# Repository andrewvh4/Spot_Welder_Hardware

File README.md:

# Spot_Welder_Hardware
A Design for a low-cost spot welder used in electronics assembly

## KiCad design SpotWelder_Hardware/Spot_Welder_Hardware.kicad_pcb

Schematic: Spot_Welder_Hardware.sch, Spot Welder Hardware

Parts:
BZ1: Buzzer; BUZZER_SMI_1324_TW_5V_2_R; Part Number 668-1336-1-ND
C1, C2, C3, C4, C5, C6, C8, C9, C10, C12, C13, C14, C16, C17, C18, C20, C21, C22, C25, C26, C27, C29, C30, C31, C33, C34, C35, C36, C37, C38, C45: 47mF; CP_Radial_D30.0mm_P10.00mm_SnapIn; Part Number 565-2620-ND
C7, C11, C15, C19, C23, C24, C28, C32: C; C_0805_HandSoldering
C39, C40, C46, C47, C48: .1uF; C_0603_HandSoldering
C41, C42: 22pF; C_0603_HandSoldering
C43, C44: 10uF; C_0603_HandSoldering
Conn1, Conn2: BananaConnector; Banana_Jack_1Pin
Conn3: AndersonPP; Anderson_2_Horisontal_Side_by_Side
Conn4: Molex_SL_3; MOLEX_SL_3_Horizontal
D1: 5V; LED_0603_HandSoldering
D2: Pulse; LED_0603_HandSoldering
D3: 7.5V; LED_0603_HandSoldering
D4: Ext Trigger; LED_0603_HandSoldering
D5: 10V; LED_0603_HandSoldering
D6: Logic; LED_0603_HandSoldering
D7: 12.5V; LED_0603_HandSoldering
D8, D9: D_Schottky; D_0603_1608Metric_Pad1.05x0.95mm_HandSolder
D10: 14V; D_SOD-123; Part Number BZT52C15-FDICT-ND
D11: Over Voltage; LED_0603_HandSoldering
D12: 20V; D_SOD-123; Part Number B0520LW-FDICT-ND
D13: D; TO-220-2_Vertical; Part Number MUR1560GOS-ND
D14, D15, D16, D19: D; TO-220-2_Vertical
D17: TX; LED_0603_HandSoldering
D18: RX; LED_0603_HandSoldering
D20: FTDI PWR; LED_0603_HandSoldering
J1: Mini USB; MiniUSB_SMT; Part Number 151-1206-1-ND
J2: Conn_01x03_Male; Pin_Header_Straight_1x03_Pitch2.54mm
L1: Ferrite_Bead; L_0603_HandSoldering; Part Number 732-1593-1-ND
L2, L3, L4, L5, L6, L7, L8, L9, L10: Ferrite_Bead; L_0603_HandSoldering
Q1: Q_NMOS_GSD; SOT-323_SC-70_Handsoldering; Part Number 2N7002PW
Q2: MBT3904; SOT-23
Q3, Q4, Q5, Q6, Q7, Q8, Q9, Q10, Q11, Q12, Q13: Q_NMOS_GDS; TO-220-3_Vertical; Part Number PSMN1R1
R1, R3, R5, R6, R7, R8, R9: 500; R_0603_HandSoldering
R2, R17, R22, R27, R33: 10k; R_0603_HandSoldering
R4, R24, R25: 1k; R_0603_HandSoldering
R10, R15: 3000; R_0603_HandSoldering
R11, R16, R39, R41, R42: 1000; R_0603_HandSoldering
R12, R13, R14: 5; R_Axial_Power_L25.0mm_W6.4mm_P30.48mm; Part Number YAG1224CT-ND
R18, R20, R40: 10K; R_0603_HandSoldering
R19: 1K; R_0603_HandSoldering
R21: 250; R_0603_HandSoldering
R23, R26, R28, R29, R30, R31, R32, R34, R36, R38: 10; R_0603_HandSoldering
R35, R37: 330; R_0603_HandSoldering
SW1, SW4: SW_Push; SPST_Pushbutton; Part Number CKN9088CT-ND
SW2: SW_SPDT; SPDT_Switch; Part Number CKN9628-ND
SW3: Lead Voltage Trigger; SPST_DIP_Switch; Part Number CKN10358-ND
U1: OKI; OKI_Horisontal
U2: ATMEGA328P; DIP-28_W7.62mm; Part Number ED3050-5-ND
U3, U5: FAN3122TMXCT-ND; SOIC-8_3.9x4.9mm_Pitch1.27mm
U4: FT232RL; SSOP-28_5.3x10.2mm_Pitch0.65mm
Y1: Crystal; Crystal_SMD_HC49-SD_HandSoldering; Part Number XC1592CT-ND

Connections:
5V_Ind: R1.2, U2.15 ((PCINT1/OC1A)PB1)
7.5V_Ind: R5.2, U2.16 ((PCINT2/OC1B/~SS~)PB2)
10V_Ind: R7.2, U2.17 ((PCINT3/OC2A/MOSI)PB3)
12.5V_Ind: R9.2, U2.18 ((PCINT4/MISO)PB4)
+5V: BZ1.1 (-), C39.1, C44.2, Conn4.1, D8.1 (K), D9.1 (K), R8.2, R17.1, SW1.1, SW3.1 (A), U1.3 (Vo), U2.7 (VCC), U2.20 (AVCC), U3.3 (EN), U5.3 (EN)
/Vin: C43.1, C45.1, D12.1 (K), R21.1, U1.1 (Vi)
Buzzer: R2.1, R4.1, U2.6 ((PCINT20/XCK/T0)PD4)
Conn_GND: Conn2.1, Conn3.1 (GND), SW2.3 (C)
D+: J1.3, U4.15 (USBDP)
D-: J1.2, U4.16 (USBDM)
DTR: C48.1, J2.3, U4.2 (DTR#)
Ext_Trigger: Conn4.2, R6.2, U2.12 ((PCINT22/OC0A/AIN0)PD6)
GND: C1.2, C2.2, C3.2, C4.2, C5.2, C6.2, C7.2, C8.2, C9.2, C10.2, C11.2, C12.2, C13.2, C14.2, C15.2, C16.2, C17.2, C18.2, C19.2, C20.2, C21.2, C22.2, C23.2, C24.2, C25.2, C26.2, C27.2, C28.2, C29.2, C30.2, C31.2, C32.2, C33.2, C34.2, C35.2, C36.2, C37.2, C38.2, C39.2, C40.2, C41.2, C42.2, C43.2, C44.1, C45.2, C46.2, C47.1, Conn4.3, D1.1 (K), D2.1 (K), D3.1 (K), D4.1 (K), D5.1 (K), D6.1 (K), D7.1 (K), D20.1 (K), J1.5, Q1.2 (S), Q3.2 (D), Q4.3 (S), Q5.3 (S), Q6.3 (S), Q7.3 (S), Q8.3 (S), Q9.3 (S), Q10.3 (S), Q11.3 (S), Q12.3 (S), Q13.3 (S), R2.2, R11.2, R16.2, R21.2, R22.2, R27.2, R33.2, R41.1, R42.1, SW4.1, U1.2 (GND), U2.8 (GND), U2.22 (GND), U3.4 (GND), U3.5 (GND), U4.7 (GND), U4.18 (GND), U4.21 (GND), U4.25 (AGND), U4.26 (TEST), U5.4 (GND), U5.5 (GND)
IC_RX: J2.2, R24.1, U4.1 (TXD)
IC_TX: J2.1, R25.1, U4.5 (RXD)
Lead_Sense: D8.2 (A), R10.1, R11.1, U2.24 ((PCINT9/ADC1)PC1)
Lead_Voltage_Trigger: R42.2, SW3.2 (B), U2.13 ((PCINT23/AIN1)PD7)
unnamed: BZ1.2 (+), Q1.3 (D)
unnamed: C40.1, U2.21 (AREF)
unnamed: C41.1, U2.9 ((PCINT6/XTAL1/TOSC1)PB6), Y1.1
unnamed: C42.1, U2.10 ((PCINT7/XTAL2/TOSC2)PB7), Y1.2
unnamed: C46.1, U4.17 (3V3_Out)
unnamed: D1.2 (A), R1.1
unnamed: D2.2 (A), R3.1
unnamed: D3.2 (A), R5.1
unnamed: D4.2 (A), R6.1
unnamed: D5.2 (A), R7.1
unnamed: D6.2 (A), R8.1
unnamed: D7.2 (A), R9.1
unnamed: D10.2 (A), R19.2
unnamed: D11.1 (K), R40.2
unnamed: D17.1 (K), U4.22 (CBUS1)
unnamed: D17.2 (A), R35.2
unnamed: D18.1 (K), U4.23 (CBUS0)
unnamed: D18.2 (A), R37.2
unnamed: D20.2 (A), R39.2
unnamed: L1.1, Q4.1 (G)
unnamed: L1.2, R23.1
unnamed: L2.1, Q5.1 (G)
unnamed: L2.2, R26.1
unnamed: L3.1, Q6.1 (G)
unnamed: L3.2, R28.1
unnamed: L4.1, Q7.1 (G)
unnamed: L4.2, R29.1
unnamed: L5.1, Q8.1 (G)
unnamed: L5.2, R30.1
unnamed: L6.1, Q9.1 (G)
unnamed: L6.2, R31.1
unnamed: L7.1, Q10.1 (G)
unnamed: L7.2, R32.1
unnamed: L8.1, Q11.1 (G)
unnamed: L8.2, R34.1
unnamed: L9.1, Q12.1 (G)
unnamed: L9.2, R36.1
unnamed: L10.1, Q13.1 (G)
unnamed: L10.2, R38.1
unnamed: Q1.1 (G), R4.2
unnamed: Q2.1 (B), R19.1, R20.1
unnamed: Q2.3 (C), Q3.1 (G), R18.1, R40.1
unnamed: R12.1, R13.2
unnamed: R12.2, SW2.1 (A)
unnamed: R13.1, R14.2
unnamed: R23.2, R26.2, R28.2, R29.2, R30.2, U3.6 (Out), U3.7 (Out)
unnamed: R24.2, U2.2 ((PCINT16/RXD)PD0)
unnamed: R25.2, U2.3 ((PCINT17/TXD)PD1)
unnamed: R31.2, R32.2, R34.2, R36.2, R38.2, U5.6 (Out), U5.7 (Out)
Power_GND: Q2.2 (E), Q3.3 (S), R20.2, SW2.2 (B)
Pulse_Out: R3.2, R27.1, R33.1, R41.2, SW1.2, U2.11 ((PCINT21/OC0B/T1)PD5), U3.2 (IN), U5.2 (IN)
Reset: C48.2, R17.2, SW4.2, U2.1 ((PCINT14/~RESET~)PC6)
USB+5V: C47.2, J1.1, R35.1, R37.1, R39.1, U4.4 (VCCIO), U4.19 (RESET#), U4.20 (VCC)
V+: C1.1, C2.1, C3.1, C4.1, C5.1, C6.1, C7.1, C8.1, C9.1, C10.1, C11.1, C12.1, C13.1, C14.1, C15.1, C16.1, C17.1, C18.1, C19.1, C20.1, C21.1, C22.1, C23.1, C24.1, C25.1, C26.1, C27.1, C28.1, C29.1, C30.1, C31.1, C32.1, C33.1, C34.1, C35.1, C36.1, C37.1, C38.1, Conn1.1, Conn3.2 (V+Log), D10.1 (K), D11.2 (A), D12.2 (A), D13.1 (K), D14.1 (K), D15.1 (K), D16.1 (K), D19.1 (K), R14.1, R15.2, R18.2, U3.1 (VDD), U3.8 (VDD), U5.1 (VDD), U5.8 (VDD)
VS: D13.2 (A), D14.2 (A), D15.2 (A), D16.2 (A), D19.2 (A), Q4.2 (D), Q5.2 (D), Q6.2 (D), Q7.2 (D), Q8.2 (D), Q9.2 (D), Q10.2 (D), Q11.2 (D), Q12.2 (D), Q13.2 (D), R10.2, R22.1
V_Sense: D9.2 (A), R15.1, R16.1, U2.23 ((PCINT8/ADC0)PC0)

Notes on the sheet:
Main Capacitor Bank
External Connections
Power Input
External Trigger
Open Drain
Power Filtering
Indication
Microcontroller
FTDI
Capacitor Voltage Read
Voltage Indication
ToDo: Find capacitance
Lead Voltage Read
Trigger Override
Interface
Lead-Voltage Trigger
ADC 0
ADC 1
Used to toggle lead voltage trigger mode
D12
D11
D10
Serial Headers
USB
Logic Power
On/Off
Power
Trigger
Voltage Read
Over-Voltage Protection
30 parallel capacitors @4700uF and 14mOhm ESR yields 1.41F and .47mOhm ESR
Active Low
Safety Short VS to Ground
at 15Ohm and 1.4F, t = 10s 5t = 50s At 15V, each resistor will carry 5W

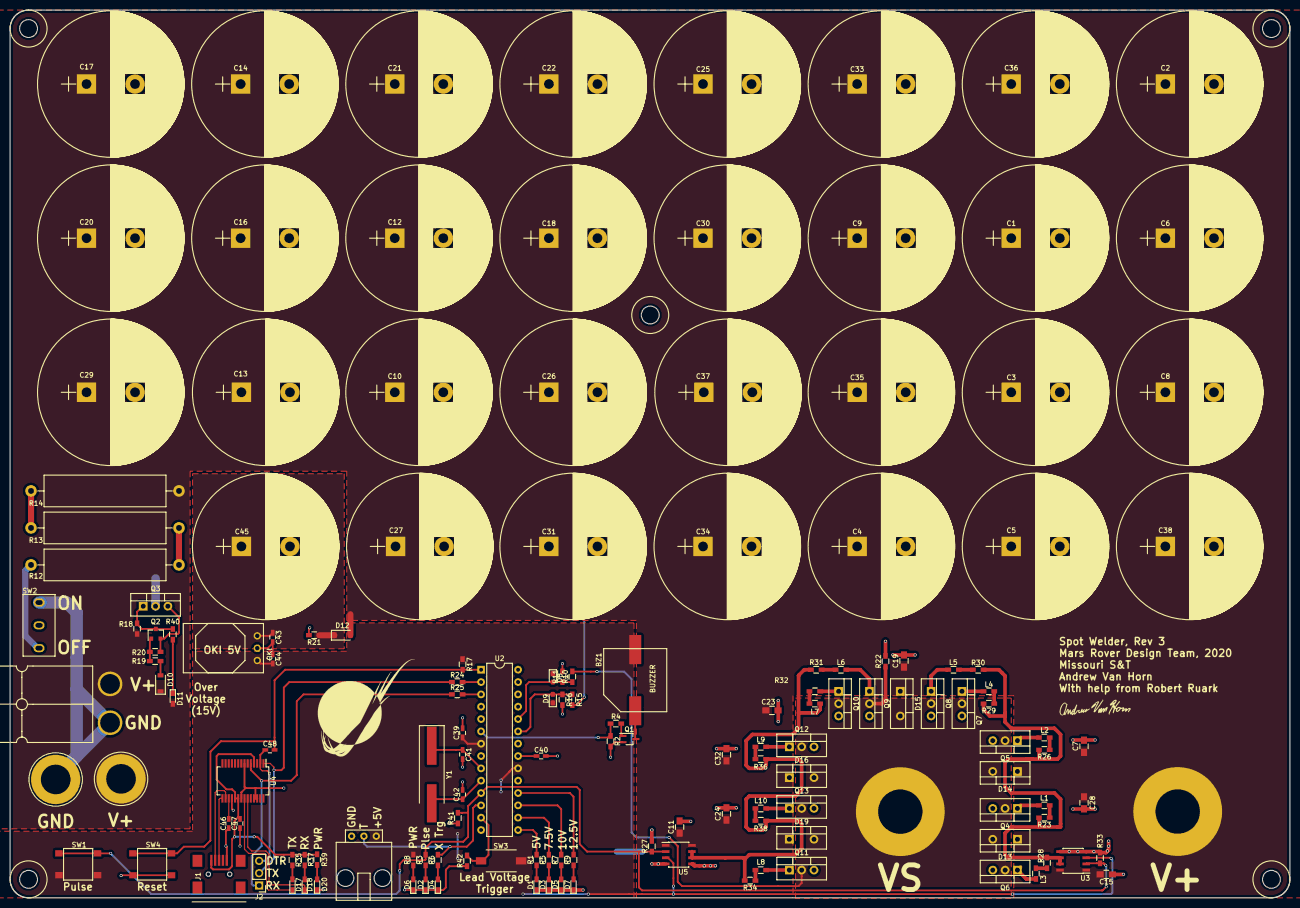
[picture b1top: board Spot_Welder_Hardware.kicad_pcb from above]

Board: 2 copper layers, 263.7 x 182.9 mm, 150 parts (0 on the bottom side), 73 nets.

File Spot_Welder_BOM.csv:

Id,Designator,Package,Designation,,Item Name,Part Number,,,Vendor,Quantity,Cost Per Item,,Cost,,Comments,URL
1,BZ1,BUZZER_SMI_1324_TW_5V_2_R,Buzzer,,Buzzer,668-1336-1-ND,,,Digikey,1,6.12,,6.12,,,https://www.digikey.com/products/en?keywords=668-1336-1-ND
2,"C1,C2,C3,C4,C5,C6,C8,C9,C10,C12,C13,C14,C16,C17,C18,C20,C21,C22,C25,C26,C27,C29,C30,C31,C33,C34,C35,C36,C37,C38,C45",CP_Radial_D30.0mm_P10.00mm_SnapIn,47mF,,47mF Capacitor,565-2620-ND,,,Digikey,31,4.2,,130.2,,,https://www.digikey.com/products/en?keywords=565-2620-ND
3,"C7,C11,C15,C19,C23,C24,C28,C32",C_0805_HandSoldering,C,,10uF 0603 Capacitor,490-10728-1-ND,,,Digikey,8,0.32,,2.56,,,https://www.digikey.com/product-detail/en/murata-electronics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
4,"C39,C40,C46,C47,C48",C_0603_HandSoldering,.1uF,,.1uF 0603 Capacitor,1276-1258-1-ND,,,Digikey,5,0.1,,0.5,,,https://www.digikey.com/product-detail/en/samsung-electro-me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
5,"C41,C42",C_0603_HandSoldering,22pF,,22pF 0603 Capacitor,399-9031-1-ND,,,Digikey,2,0.1,,0.2,,,https://www.digikey.com/product-detail/en/kemet/C0603C220K4G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
6,"C43,C44",C_0603_HandSoldering,10uF,,10uF 0603 Capacitor,490-10728-1-ND,,,Digikey,2,0.32,,0.64,,,https://www.digikey.com/product-detail/en/murata-electronics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
7,"Conn1,Conn2",Banana_Jack_1Pin,BananaConnector,,,,,,Digikey,2,,,0,,,
8,Conn3,Anderson_2_Horisontal_Side_by_Side,Anderson_2,,,,,,Digikey,1,,,0,,,
9,Conn4,MOLEX_SL_3_Horizontal,Molex_SL_3,,Molex SL-3,WM4901-ND,,,Digikey,1,1.06,,1.06,,,https://www.digikey.com/product-detail/en/molex-llc/07055300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
10,D1,LED_0603_HandSoldering,5V,,LED 0603 Yellow,350-2032-1-ND,,,Digikey,1,0.51,,0.51,,,https://www.digikey.com/product-detail/en/dialight/598804010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
11,D2,LED_0603_HandSoldering,Pulse,,LED 0603 Green,160-1446-1-ND,,,Digikey,1,0.29,,0.29,,,https://www.digikey.com/product-detail/en/lite-on-inc/LTST-C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
12,D3,LED_0603_HandSoldering,7.5V,,LED 0603 Yellow,350-2032-1-ND,,,Digikey,1,0.51,,0.51,,,https://www.digikey.com/product-detail/en/dialight/598804010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
13,D4,LED_0603_HandSoldering,Ext Trigger,,LED 0603 Green,160-1446-1-ND,,,Digikey,1,0.29,,0.29,,,https://www.digikey.com/product-detail/en/lite-on-inc/LTST-C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
14,D5,LED_0603_HandSoldering,10V,,LED 0603 Green,160-1446-1-ND,,,Digikey,1,0.29,,0.29,,,https://www.digikey.com/product-detail/en/lite-on-inc/LTST-C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
15,D6,LED_0603_HandSoldering,Logic,,LED 0603 Green,160-1446-1-ND,,,Digikey,1,0.29,,0.29,,,https://www.digikey.com/product-detail/en/lite-on-inc/LTST-C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
16,D7,LED_0603_HandSoldering,12.5V,,LED 0603 Green,160-1446-1-ND,,,Digikey,1,0.29,,0.29,,,https://www.digikey.com/product-detail/en/lite-on-inc/LTST-C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
17,"D8,D9",D_0603,Shottky,,Shottky Diode 0603,478-7798-1-ND,,,Digikey,1,46,,46,,,https://www.digikey.com/product-detail/en/avx-corporation/SD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
18,D10,D_SOD-123,15V,,15V Zener Diode,BZT52C15-FDICT-ND,,,Digikey,1,0.24,,0.24,,,https://www.digikey.com/products/en?keywords=BZT52C15-FDICT-ND
19,D11,LED_0603_HandSoldering,Over Voltage,,LED 0603 Red,475-2512-1-ND,,,Digikey,1,0.38,,0.38,,,https://www.digikey.com/product-detail/en/osram-opto-semicon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
20,D12,D_SOD-123,20V,,20V Shottkey Diode,B0520LW-FDICT-ND,,,Digikey,1,0.36,,0.36,,,https://www.digikey.com/products/en?keywords=B0520LW-FDICT-ND
21,"D13,D14,D15,D16,D19",TO-220-2_Vertical,D,,Highspeed High Current Diode,MUR1560GOS-ND,,,Digikey,5,1.39,,6.95,,,https://www.digikey.com/products/en?keywords=MUR1560GOS-ND
22,D17,LED_0603_HandSoldering,TX,,LED 0603 Green,160-1446-1-ND,,,Digikey,1,0.29,,0.29,,,https://www.digikey.com/product-detail/en/lite-on-inc/LTST-C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
23,D18,LED_0603_HandSoldering,RX,,LED 0603 Green,160-1446-1-ND,,,Digikey,1,0.29,,0.29,,,https://www.digikey.com/product-detail/en/lite-on-inc/LTST-C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
24,D20,LED_0603_HandSoldering,FTDI PWR,,LED 0603 Green,160-1446-1-ND,,,Digikey,1,0.29,,0.29,,,https://www.digikey.com/product-detail/en/lite-on-inc/LTST-C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
25,J1,MiniUSB_SMT,Mini USB,,SMD Mini USB,151-1206-1-ND,,,Digikey,1,0.54,,0.54,,,https://www.digikey.com/product-detail/en/edac-inc/690-005-2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
26,J2,Pin_Header_Straight_1x03_Pitch2.54mm,Conn_01x03_Male,,,,,,Digikey,1,,,0,,,
27,"L1,L2,L3,L4,L5,L6,L7,L8,L9,L10",L_0603_HandSoldering,Ferrite_Bead,,Ferrite Bead,732-1593-1-ND,,,Digikey,10,0.17,,1.7,,,https://www.digikey.com/products/en?keywords=732-1593-1-ND
28,Q1,SOT-323_SC-70_Handsoldering,Q_NMOS_GSD,,2N7002PW,1727-4793-1-ND,,,Digikey,1,0.33,,0.33,,,https://www.digikey.com/product-detail/en/nexperia-usa-inc/2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
29,Q2,SOT-23,MBT3904,,MBT3904 NPN BJT,MMBT3904TPMSTR-ND,,,Digikey,1,0.1,,0.1,,,https://www.digikey.com/product-detail/en/micro-commercial-c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
30,"Q3,Q4,Q5,Q6,Q7,Q8,Q9,Q10,Q11,Q12,Q13",TO-220-3_Vertical,Q_NMOS_GDS,,NMOSFET-PSMN1R1-30PL,1727-5291-ND,,,Digikey,11,3.39,,37.29,,,https://www.digikey.com/products/en?keywords=PSMN2R0-30PL
31,"R1,R3,R5,R6,R7,R8,R9",R_0603_HandSoldering,500,,0603 Resistor 500,RHM510DCT-ND,,,Digikey,7,0.1,,0.7,,,https://www.digikey.com/product-detail/en/rohm-semiconductor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
32,"R2,R17,R22,R27,R33",R_0603_HandSoldering,10k,,0603 Resistor 10K,RHM10KADCT-ND,,,Digikey,5,0.1,,0.5,,,https://www.digikey.com/product-detail/en/rohm-semiconductor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
33,"R4,R24,R25",R_0603_HandSoldering,1k,,0603 Resistor 1K,RHM1.0KDCT-ND,,,Digikey,3,0.1,,0.3,,,https://www.digikey.com/product-detail/en/rohm-semiconductor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
34,"R10,R15",R_0603_HandSoldering,3000,,0603 Resistor 3K,MCT0603-3.00K-CFCT-ND,,,Digikey,2,0.18,,0.36,,,https://www.digikey.com/product-detail/en/vishay-beyschlag/M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
35,"R11,R16, R39",R_0603_HandSoldering,1000,,0603 Resistor 1K,RHM1.0KDCT-ND,,,Digikey,3,0.1,,0.3,,,https://www.digikey.com/product-detail/en/rohm-semiconductor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
36,"R12,R13,R14",R_Axial_Power_L25.0mm_W6.4mm_P30.48mm,5,,5 Ohm Resistor,YAG1224CT-ND,,,Digikey,3,0.72,,2.16,,,https://www.digikey.com/products/en?keywords=YAG1224CT-ND
37,"R18,R20, R40",R_0603_HandSoldering,10K,,0603 Resistor 10K,RHM10KADCT-ND,,,Digikey,3,0.14,,0.42,,,https://www.digikey.com/product-detail/en/rohm-semiconductor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
38,R19,R_0603_HandSoldering,1K,,0603 Resistor 1K,RHM1.0KDCT-ND,,,Digikey,1,0.1,,0.1,,,https://www.digikey.com/product-detail/en/rohm-semiconductor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
39,R21,R_0603_HandSoldering,250,,0603 Resistor 250,P249BLCT-ND,,,Digikey,1,0.13,,0.13,,,https://www.digikey.com/product-detail/en/panasonic-electron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
40,"R23,R26,R28,R29,R30,R31,R32,R34,R36,R38",R_0603_HandSoldering,10,,0603 Resistor 10K,RHM10.0ADCT-ND,,,Digikey,10,0.12,,1.2,,,https://www.digikey.com/product-detail/en/rohm-semiconductor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
41,"R35,R37",R_0603_HandSoldering,330,,0603 Resistor 330,311-330HRCT-ND,,,Digikey,3,0.1,,0.3,,,https://www.digikey.com/product-detail/en/yageo/RC0603FR-073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
42,"SW1,SW4",SPST_Pushbutton,SW_Push,,Pushbutton Switch,CKN9088CT-ND,,,Digikey,2,0.22,,0.44,,,https://www.digikey.com/products/en?keywords=CKN9088CT-ND
43,SW2,SPDT_Switch,SW_SPDT,,SPDT Switch,CKN9628-ND,,,Digikey,1,5.34,,5.34,,,https://www.digikey.com/products/en?keywords=CKN9628-ND
44,SW3,SPST_DIP_Switch,Lead Voltage Trigger,,SPST DIP Switch,CKN10358-ND,,,Digikey,1,1.19,,1.19,,,https://www.digikey.com/products/en?keywords=CKN10358-ND
45,U1,OKI_Horisontal,OKI,,5V OKI,811-2692-ND,,,Digikey,1,4.3,,4.3,,,https://www.digikey.com/product-detail/en/murata-power-solut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
46,,,ATMEGA328P,,ATMEGA328PU,ATMEGA328-PU-ND,,,Digikey,1,1.96,,1.96,,,https://www.digikey.com/product-detail/en/microchip-technolo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
47,U2,DIP-28_W7.62mm,,,ATMEGA 328 Housing,ED3050-5-ND,,,Digikey,1,0.33,,0.33,,,https://www.digikey.com/products/en?keywords=ED3050-5-ND
48,"U3,U5",SOIC-8_3.9x4.9mm_Pitch1.27mm,FAN3122TMXCT-ND,,GateDriver,FAN3122TMXCT-ND,,,Digikey,2,1.61,,3.22,,,https://www.digikey.com/products/en?keywords=FAN3122TMXCT-ND
49,U4,SSOP-28_5.3x10.2mm_Pitch0.65mm,FT232RL,,FTDI,FT232RL,,,Digikey,1,4.5,,4.5,,,https://www.digikey.com/product-detail/en/ftdi-future-techno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
50,Y1,Crystal_SMD_HC49-SD_HandSoldering,Crystal,,8MHz Crystal,XC1592CT-ND,,,Digikey,1,1.71,,1.71,,,https://www.digikey.com/products/en?keywords=XC1592CT-ND
51,,,,,PCB,,,,JLCPCB,1,6,,6,,,
Total,,,,,,,,,,,,,211.42,,,

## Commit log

2018-06-29 Rough Schematic
    Still need to double check component values before review.
2018-06-30 modified component values
    Final touchups before schematic review.
2018-06-30 Added Buzzer circuitry
2018-06-30 Added Buzzer Part number
2018-06-30 Minor Formatting Tweaks
2018-07-04 Added Voltage Limiting Circuitry and annotation
2018-08-15 Finalized BOM
2018-08-29 Created ToDo
2018-09-24 Started board layout
2018-09-25 High-lvel power placemet
2018-09-28 Placed components and routed all signal
2018-09-28 Moved around Components
2018-09-28 Created Polygons
2018-09-28 Finished Fill Zones and grounding
2018-09-28 re-routed 5V to Lead Voltage Trigger
2018-09-29 Modified OverVoltage Protection LED
2018-09-29 Added 6-32 Mounting Holes
2018-09-29 Fixed Vias on crystal caps
2018-09-29 Moved second gate driver closer to the ransistors
2018-09-29 Moved VS sense trace
2018-09-29 Swapped main MOSFETs to PSMN1R1-30PL
2018-09-29 Modified Analog limiter circuit for analogue reads
2018-09-29 Brke up ground plane for digital circuitry
2018-09-29 Changes Resistor To 1K
2018-09-29 Changed Gate Driver Power to V+
2018-09-29 Moved Gate Driver closer to MOSFETs
2018-09-29 Changed BJT
2018-09-29 Frew new Traces for change in schematic
2018-09-29 Finished Silkscreen
2018-09-29 Re-routed LED indications in ATMEGA
2018-09-29 Updated BOM
2018-09-30 Fixed outline and mounting holes
2018-09-30 Replaced D8, D9 with Shottky Diode
2018-09-30 Moved around ground planes
2018-09-30 Routed Ground Plane
2018-09-30 Modified Schematic
2018-09-30 Modified gitignore and added BOM
2018-10-01 Updated 6-32 Hole Size
2018-11-20 Mino changes from Assembly
2018-11-21 Updated todo
2018-11-21 Updated shematic libraries
2018-11-21 Added pulldown Resistor to switches
2018-11-21 Fixed Layout
2018-11-21 Fixed Layout Issues
2019-01-20 Added ToDo Notes
2020-05-26 Cleaned repo structure and updated library mappings
2020-05-26 Changed OverV sense zener to 14V to provide better tolerance after testing.
2020-05-26 Added center support hole
2020-05-26 Inc version number and generated gerbs
2020-05-26 Updated version number
2020-05-26 renumbered BOM
2020-05-26 Updated 0805 Cap Value
